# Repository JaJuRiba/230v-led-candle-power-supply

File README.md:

# 230 V Mains-Powered LED Candle Supply — V1

**Concept only. No 230 V schematic, installation approval, or manufacturing release.**

The eventual design takes 230 V AC mains input and provides a shared, securely configurable, isolated DC voltage for one to five LED candles, with individual protection for each output. A separate Shelly relay is intended to handle scheduling in the eventual installation. The final power-supply rating is open. The first prototype uses only low-voltage DC from an external, isolated, current-limited supply. The reference settings are 3.0 V and 4.5 V; the 1.5–6 V range is optional.

```mermaid
flowchart LR
    A[External isolated DC supply] --> B[Shared voltage regulation and monitoring]
    B --> C[Up to five individually protected outputs]
    C --> D[Reference loads, then LED candles with batteries removed]
```

This diagram describes the V1 goal. The A0 schematic below covers only the DC distributor.

## P1 — enclosed low-voltage controller, first-article candidate

P1 uses an **external isolated regulated 6 V supply**. The printed standalone enclosure is not a flush-mount mains enclosure. The [P1 electronics](hardware/p1/README.md) supersede the E1 bench board as the first-article target. No production qualification, regulatory approval or order is claimed.

- [JLCPCB candidate files and order checks](manufacturing/p1-candidate/README.md) · [sourcing evidence](manufacturing/p1-sourcing/README.md)
- [Enclosure: assembly, H2D print files and clearances](mechanical/p1/README.md) · [separate cable harness](docs/p1-harness.md)
- [Design assumptions](docs/p1-design-contract.md) · [physical acceptance tests](manufacturing/p1-tools/acceptance.md)

## E1 — earlier low-voltage bench prototype

[Open the editable E1 project, BOM and bench test procedure](hardware/e1/README.md). Unlike A0, E1 takes **6.10 V nominal isolated bench DC**, regulates it to a shared 3.0 or 4.5 V, and limits current independently on five outputs. No mains input or independent overvoltage cutoff. [Editable two-layer bench PCB and DRC report](hardware/e1/board/README.md). Unbuilt; not a flush-box layout or manufacturing release.

## Earlier KiCad schematic — revision A0

The [editable DC distributor schematic](230v-led-candle-power-supply.kicad_sch) targets KiCad 10.0.8. J1 receives 3.0 V or 4.5 V directly from an isolated, current-limited bench supply. F1–F5 show where branch protection is intended; no fuses have been selected or approved. A0 does not implement voltage regulation, overvoltage protection, or reverse-polarity protection. It has not been built or tested with candles.

The [A0 ERC report](docs/erc-a0.json) shows zero violations in KiCad 10.0.8. The KiCad netlist also contains all seven expected nets. These checks do not approve the design for construction or installation.

## Low-voltage test plan

**E1 design assumption:** budget 20 mA per candle in normal operation and design the distributor for 50 mA continuous per output at either voltage (250 mA total; up to 1.125 W delivered at 4.5 V). This is available current, not current to force through a candle, a measured peak, or a fuse rating. The final supply must also account for conversion losses, temperature and transient response.

Two commercial examples inform the nominal assumption. The [Goobay 64786 manual](https://www.pollin.de/media/fa/6f/01/1742196926/D521850-B.pdf) specifies one LED per candle and 0.06 W/LED at a 3.0 V operating voltage. The [Goobay 74368 manual](https://www.wentronic.com/media/perfion/perfion-product/74368_Bedienungsanleitung%23Manual.pdf) specifies 0.06 W/LED and 4.5 V operation. Dividing those figures by the respective supply voltage gives 20 mA and 13.3 mA as power equivalents, **not** measured battery-terminal currents. Neither figure establishes startup peaks or covers moving-flame and multi-LED models. Use reference loads until each candle model is characterized; coin-cell candles may rely on cell impedance and are not qualified for direct connection.

| Setpoint | Load per output | Current per output | Total current for five outputs | Power per load |
|---|---:|---:|---:|---:|
| 3.0 V | 150 Ω | 20.0 mA | 100.0 mA | 0.060 W |
| 3.0 V | 60 Ω | 50.0 mA | 250.0 mA | 0.150 W |
| 4.5 V | 225 Ω | 20.0 mA | 100.0 mA | 0.090 W |
| 4.5 V | 91 Ω | 49.45 mA | 247.25 mA | 0.223 W |

The figures follow from I = V/R and P = V²/R. Use 1% resistors rated for at least 0.5 W, with adequate ventilation and appropriate derating. These are reference loads, not measured candle characteristics. The test plan does not cover 6 V.

1. At each setpoint, test with no load, one output loaded, and five outputs loaded. Test power-up and load steps. Record current, temperature, and voltage at the supply or regulator and at the farthest load. Use an oscilloscope to capture brief spikes.
2. After branch protection has been implemented, use only reference loads and a current-limited source to test a short on one output. Record the fault current and the behavior of the other outputs. The target is to limit or disconnect the faulty output without driving the others outside their acceptable range. Verify this with the common supply current limit in effect.
3. Evaluate reverse polarity, incorrect voltage selection, and regulator failure separately. Overvoltage protection must match the selected output: a fixed 6 V threshold cannot protect a 3 V candle. Record overload behavior and temperature. No hardware tests have been performed yet.
4. For each selected candle, check polarity, steady-state and peak currents, timer behavior, and restart after loss of power. A regulated supply can deliver more current than a coin cell; nominal battery voltage alone is not enough. Remove batteries before applying external power. Establish acceptable voltage and current limits before finalizing the design.

## Flush-mount box fit study

[Print the two M0 fit gauges and follow the loose-box test](mechanical/README.md). Digitally checked. In one physical trial, the operator reported that the printed bodies went in loosely in the tested orientation. Remaining depth and fit with the cover were not measured. These blocks represent only the relay and module bodies, not the complete assembly.

The reference box is the **KAISER UP¹ 1555-05** (EAN 4013456594937). The [KAISER data sheet](https://www.kaisergroup.com/assets/media/21/21577/Datasheet_1555-05_%28EAN_4013456594937%29_en_KAISER.pdf) lists a 66 mm product depth, a 60 mm diameter device opening, an 82 mm diameter wall cutout, and four groups of three screw bosses. The 82 mm dimension is not an internal diameter. [Elektrikshop](https://www.elektrikshop.de/kaiser-unterputzdosen-up1-1555-05-tief.html) lists 65 mm of internal depth; that is not the usable space after adding a cover, terminals, and wiring.

The reported clear width and usable depth are approximately **54 mm and 64 mm**, respectively. The [to-scale preliminary fit study](fit-study-1555-05.svg) assumes an ideal cylinder; a 54 mm clear diameter across its full depth has not been established. The [KAISER CAD portal entry](https://kaiser.partcommunity.com/?languageIso=en&catalog=kaiser&part=1555-05) is available, but the model download was blocked in this environment.

The [Shelly 1 Mini Gen3](https://www.shelly.com/products/shelly-1-mini-gen3) measures 29 × 34 × 16 mm nominally. The [PCB-mount Mean Well IRM-03](https://www.meanwell.com/Upload/PDF/IRM-03/IRM-03-SPEC.PDF) measures 37 × 24 × 15 mm. Their footprint diagonals are 44.7 mm and 44.1 mm, respectively, so each bare bounding box fits in the idealized cross-section on its own. Their thicknesses add up to 31 mm. The remaining 33 mm is a nominal depth budget, not confirmed clearance: it excludes the PCB, pins, enclosure, terminals, cable routing, and required spacing. This is not a proposed mounting arrangement or proof of fit.

A 3D study must account for the actual box profile, cover, screw bosses, relay, power supply, PCB, enclosure, terminals, and cable bends. Check the insertion path, terminal access, and collisions. Geometric fit does not establish electrical separation, protection against contact, or adequate cooling. A remotely mounted supply remains an option. A qualified electrician must assess the fixed installation, including the applicable overvoltage category, protection, and enclosure, before any mains PCB layout or installation.

## Components and manufacturing

Preliminary candidates: [Mean Well IRM-03-5 / IRM-03-9](https://www.meanwell.com/Upload/PDF/IRM-03/IRM-03-SPEC.PDF), [Diodes AP63201WU-7](https://www.diodes.com/part/view/AP63201), and [Shelly 1 Mini Gen3](https://www.shelly.com/products/shelly-1-mini-gen3). The IRM-03's overvoltage category II rating does not by itself establish suitability for this installation. A buck converter cannot produce 6 V from a 5 V input. Producing 4.5 V from 5 V requires verifying regulation headroom under supply tolerances and load. No power module has been selected.

For JLCPCB assembly, verify availability, LCSC part numbers, footprints, polarity, and the planned SMT or through-hole process before ordering. Generate Gerbers, the BOM, and component placement data only from the reviewed design. Open inputs: usable box geometry, the actual candle model, maximum cable length, and connector type.

See the [development plan](docs/development-plan.md) for the remaining work.

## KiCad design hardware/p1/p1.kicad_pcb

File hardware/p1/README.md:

# P1 — isolated DC five-output distributor

**CAD-checked prototype, not released for ordering, installation or candle use.** Open [p1.kicad_pro](p1.kicad_pro): [editable schematic](p1.kicad_sch), [routed PCB](p1.kicad_pcb), [schematic SVG](preview/p1.svg), [top copper](preview/front.svg), [bottom copper, viewed through board](preview/back.svg), [assembled STEP](mechanical/p1.step). [BOM with exact MPNs](bom.csv), [ERC](erc.rpt), [saved-board DRC including parity](drc.rpt), [independent pin/assembly audit](audit.py). No 230 V circuitry. Keep mains switching, source and wiring outside the printed case.

## Mechanical and harness interface

|Target|P1 design achieved / qualification gap|
|---|---|
|38 × 34 × 1.6 mm, slide-in|Rectangular straight Edge.Cuts from **(100,80) to (138,114) mm** in KiCad. No mounting holes, no bottom components. Reserve first/last 1 mm of X for insulating edge guides. Copper is **not** a mechanical insulation surface. Provide a stop and lid restraint; verify board-thickness tolerance, insertion and extraction with both plugs. No assumed enclosure offset in Z.|
|Four layers|JLC04161H-7628 1.6 mm class, 1 oz outer / 0.5 oz inner nominal. F signal plus GND spreader / In1 continuous GND / In2 VSEL / B GND with short signal crossovers, **not** a pure bottom plane. Standard stack geometry copied, not impedance-designed. Confirm chosen stack option at quotation.|
|One cable exit|One keyed 2-way DC input and a different-width keyed 10-way five-pair output, both horizontal JST SH, toward **+Y**. Bundle and strain-relieve both leads at one exit, do not use SMT hold-downs for strain relief. Mate/service only with cover open and power off.|
|50 mA × 5|Shared selectable voltage rail and five independent fault-limited outputs; not five LED current sources. 250 mA design load, 0.75/1.125 W delivered. Not tested.|

Coordinates below are **mm from top-left outline, looking down on components, +X right, +Y toward plugs**. Add (100,80) for absolute PCB coordinates. STEP export subtracts that XY origin and STEP +Y is opposite KiCad +Y. Register case geometry to the board solid rather than assuming its Z datum. All footprint placement rotations 0°. J1 center (6,30.7), J2 center (25,30.7). Signal lands at Y=28.7. Each anchor pair (MP) is grounded, not a harness terminal.

|Function|Switch pin|J pin + / return|Pad X + / return|
|---|---|---|---|
|6 V input|Q1 drain|J1.1 / J1.2|5.5 / 6.5|
|OUT1|U2.6|J2.1 / J2.2|20.5 / 21.5|
|OUT2|U3.6|J2.3 / J2.4|22.5 / 23.5|
|OUT3|U4.6|J2.5 / J2.6|24.5 / 25.5|
|OUT4|U5.6|J2.7 / J2.8|26.5 / 27.5|
|OUT5|U6.6|J2.9 / J2.10|28.5 / 29.5|

BOM J1/J2 **SM02B-SRSS-TB(LF)(SN)** / **SM10B-SRSS-TB(LF)(SN)**. Mate **SHR-02V-S-B** / **SHR-10V-S-B**, contacts **SSH-003T-P0.2-H**. [JST SH series drawing](https://www.jst-mfg.com/product/pdf/eng/eSH.pdf): side-entry header mounting height 2.95 mm; nominal bodies 4/12 mm wide; pitch 1 mm, 50 V, 1 A with AWG28. Use AWG28 stranded copper in the contact's 0.4–0.8 mm insulation range. Do **not** crimp 0.14 mm² cable directly: splice short keyed pigtails to ≥0.14 mm² trunk/branch cable outside the guide path. At 1 m each way, 0.14 mm² copper alone drops ~12.5 mV at 50 mA; add crimps, pigtails, splices, temperature and switch loss. Continuity-test cavity numbers from mating drawing: wire-side views can be mirrored. P1 does not supply crimp assemblies. Allocate a provisional 12 mm straight service space beyond +Y edge then route bends; verify actual extraction stroke, wire bend and gland with hardware. Plug body/cable absent from STEP. Tallest expected package is U1 DDPAK (reserve 5 mm above board, plus lid and assembly tolerance). Measure first article before fixing enclosure tolerances.

## Power and fault budgets

Specify a **separately qualified regulated isolated 6 V SELV adapter**, 1 A class. J1 operating envelope **5.70–6.30 V at the pins including ripple and leads**, no-load to load; do not substitute an unregulated wall wart. Example sourcing family: [GlobTek GTM41134-06VV-Q](https://www.globtek.com/ds/medical-ict-ite-household-use-power-supply/wall-plug-in/Xhu9OyH7tBZ/Ud5MWJvTD-Q/gtm41134-06vv-q.html), specify 6.0 V/1 A, regional plug and certified configuration. Family approvals are not approval of a particular adapter/harness; require certificate, exact order code and measured tolerance/start/stop behavior. A ±5% DC tolerance **plus** separate ripple/overshoot is not automatically within contract. TPS2553 switches operate only to 6.5 V even in a regulator pass fault. No surge suppressor or input overvoltage disconnect. Initially use isolated, current-limited bench DC (50 mA unloaded; 0.45 A when loading).

* **Q1 AO3401A** G1=return, S2=protected VIN, D3=raw positive. Body diode conducts D→S at correct polarity, channel then enhances; reversed J1 leaves it off. Not reverse-current isolation with externally driven outputs. At 0.4 A, 60 mΩ at −4.5 V gives 24 mV at datasheet test temperature; budget **60 mV total** to U1 including copper, contact variation and hot RDS(on), verify in situ.
* **U1 LT1963AEQ#TRPBF**, adjustable E-grade DDPAK, **1 SHDN tied high, 2 IN, 3 GND and tab, 4 OUT, 5 ADJ**. Q package, not E1's live-tab 1117. C1 local 1 µF, C2 positive pin 1 at OUT, 22 µF 16 V tantalum (19.8 µF initial min); local C3–C7 are extra upstream ceramics. Confirm actual impedance, low-temperature ESR, biased capacitance and load-step stability. At minimum source and guarded high maximum, 5.70−0.060−4.659 = **0.981 V** vs 0.35 V maximum dropout at 0.5 A; even the 1.5 A maximum 0.55 V leaves margin. Nominal headroom isn't the criterion.
* Top feedback R1=1.47 kΩ; lower R2=1.00 kΩ permanently connected. JP1 closes R3=1.18 kΩ to GND in parallel with R2. Divider draws ≥1.17 mA, above 1 mA reference test floor even with open outputs. ADJ bias flows into pin. R9 samples pre-switch rail on VSEL copper independently of ADJ; R10 permanent ground return. R11=**17.4 kΩ**, changed from study's 18.2 kΩ: original high minimum release around 4.653 V can be below this regulator's normal upper corner. JP2 closes independent OVP lower leg. No fault output is fed back into U1 regulation.
* **U7 TPS3700DDCR**: 1 OUTA NC, 2 GND, 3 INA+ GND, 4 INB− midpoint, 5 VDD protected input with C8 100 nF, 6 OUTB open-drain BR_EN. R12 10 kΩ pulls BR_EN to VSEL. **U2–U6 TPS2553DBVR**: 1 IN=VSEL, 2 GND, 3 EN=BR_EN (not tied to IN), 4 FAULT NC, 5 ILIM via own 210 kΩ, 6 distinct OUT. DBV max 135 mΩ ⇒ 6.75 mV at 50 mA before wiring. Both TI parts have pin 1 upper-left counterclockwise numbering (DDC thin vs DBV regular; generic six-lead model for U7). Monitor pulls low against <0.65 mA in a bounded pass fault; compare VOL 0.25 V vs EN low 0.66 V. Released EN ≳2.86 V vs high threshold 1.1 V. Measure each EN.

|JP1 / JP2, both changed unpowered|Nominal VSEL|DC VSEL corners|Disable rising|Release falling|
|---|---:|---:|---:|---:|
|Open / open (as produced)|2.993 V|2.892–3.100 V|3.212–3.308 V|3.139–3.276 V|
|Bridged / bridged|4.500 V|4.348–4.659 V|4.833–4.975 V|4.723–4.926 V|

[audit.py](audit.py) enumerates ±0.20% precision resistors (0.1% initial, 25 ppm/K over ±40 K), 0–1 Ω closed link, ADJ 1.174–1.246 V and 0–10 µA bias; TPS3700 rise 396–404 mV, fall 387–400 mV, design allowance ±50 nA sense leakage. DC windows exclude copper and ripple. Minimum normal-to-release margin is only ~39 mV low; qualify in case. Wrong high setting with both bridged is **not detected**. JP1 closed alone disables branches; JP2 closed alone leaves low output with the wrong high threshold. No latching, no discharge, no protection from a shorted switch or failed-low sense. Monitor can float EN high during startup/UVLO. A fast step can reach nearly fault VIN before shutdown. Threshold is **not** a peak-voltage guarantee. See [prior OVP study and bounded stimulus procedure](../../docs/ovp-study/README.md).

**Single short and heat:** 210 kΩ ±1.5% effective gives ~109–153 mA calculated DC limit; budget 154 mA. Four healthy branches + one short = 354 mA; add ≤4 mA divider, switch and detector overhead plus 25 mA regulator ground-current allowance (0.5 A test point) ⇒ **≤383 mA estimated**. Healthy-case budget ≤279 mA input. Limit calculations are not peak-current or fault-selectivity guarantees. Worst low-mode U1 loss ≈1.03 W full load, ≈1.38 W with one short; high-mode full load ≈0.66 W, including 0.158 W ground-current allowance. To keep TJ below 125 °C at 35 °C air requires effective θJA below ~88 °C/W full low, ~65 °C/W in one low-mode short. DDPAK has solid tab-to-front-ground spreader, adjacent stitching, full inner return and back ground copper; do **not** apply datasheet benchmark θJA as measured compact-enclosure performance. High-mode switch short can dissipate ~0.72 W locally; TI DBV benchmark 182.6 °C/W implies ~131 °C rise, so expect thermal cycling. Stop prolonged faults. Check U1, all switches and case to thermal equilibrium with measured ambient; design does not guarantee continuous short survival.

## Acceptance gates still open

Start with dummy loads only; no cells installed. Both modes: no load, 1 and 5 × 20/50 mA, both input extremes, startup, brownout, cable extremes and repeated branch faults. Use ≥0.5 W 60 Ω / 90 Ω resistors for nominal 50 mA low/high or programmable loads. Rotate fault across J2 pairs; record rail, all healthy far-end minima, short peak/DC, reset and temperatures. For OVP fault injection use a separate isolated test fixture or physically isolate U1 OUT before externally driving VSEL; **never parallel two supplies or force a live LDO output**. Capture EN and far-end peaks, pulse duration, automatic restart and decay at several downstream capacitances. Test all four link states. No real candle until its own permitted DC/transient envelope, polarity and impedance needs are known. No thermal, electrical or enclosure bench result claimed.

All populated parts top-side SMT; JP1/JP2 are **open copper features, not placed parts**. Candidate JLC catalog leads: [U1 C459702](https://jlcpcb.com/partdetail/AnalogDevices-LT1963AEQTRPBF/C459702), [U2–U6 C55266](https://jlcpcb.com/partdetail/C55266), [U7 C33002](https://jlcpcb.com/partdetail/C33002), [Q1 C15127](https://jlcpcb.com/partdetail/C15127). Verify exact MPN, stock, tape variant, rotations, connector mating direction/anchor solder, polarized C2 and U1 stencil/thermal pad. Do not substitute TPS2553-1 or fixed-output LT1963A. No DFM, quotes, stock reservation or assembly release. External supplier/crimp tooling and strain relief remain system items.

Sources: [ADI LT1963A pin configuration, electrical tables and applications](https://www.analog.com/media/en/technical-documentation/data-sheets/lt1963a.pdf); [AO3401A](https://www.aosmd.com/sites/default/files/res/data_sheets/AO3401A.pdf); [TI TPS3700](https://www.ti.com/lit/ds/symlink/tps3700.pdf); [TI TPS2553](https://www.ti.com/lit/ds/symlink/tps2553.pdf); [JLC stack catalog](https://jlcpcb.com/impedance). For the changed U1 test grade, R3 qualification and five-board allocation instructions see the [P1 sourcing override](../../manufacturing/p1-sourcing/README.md). See [build provenance](PROVENANCE.md).

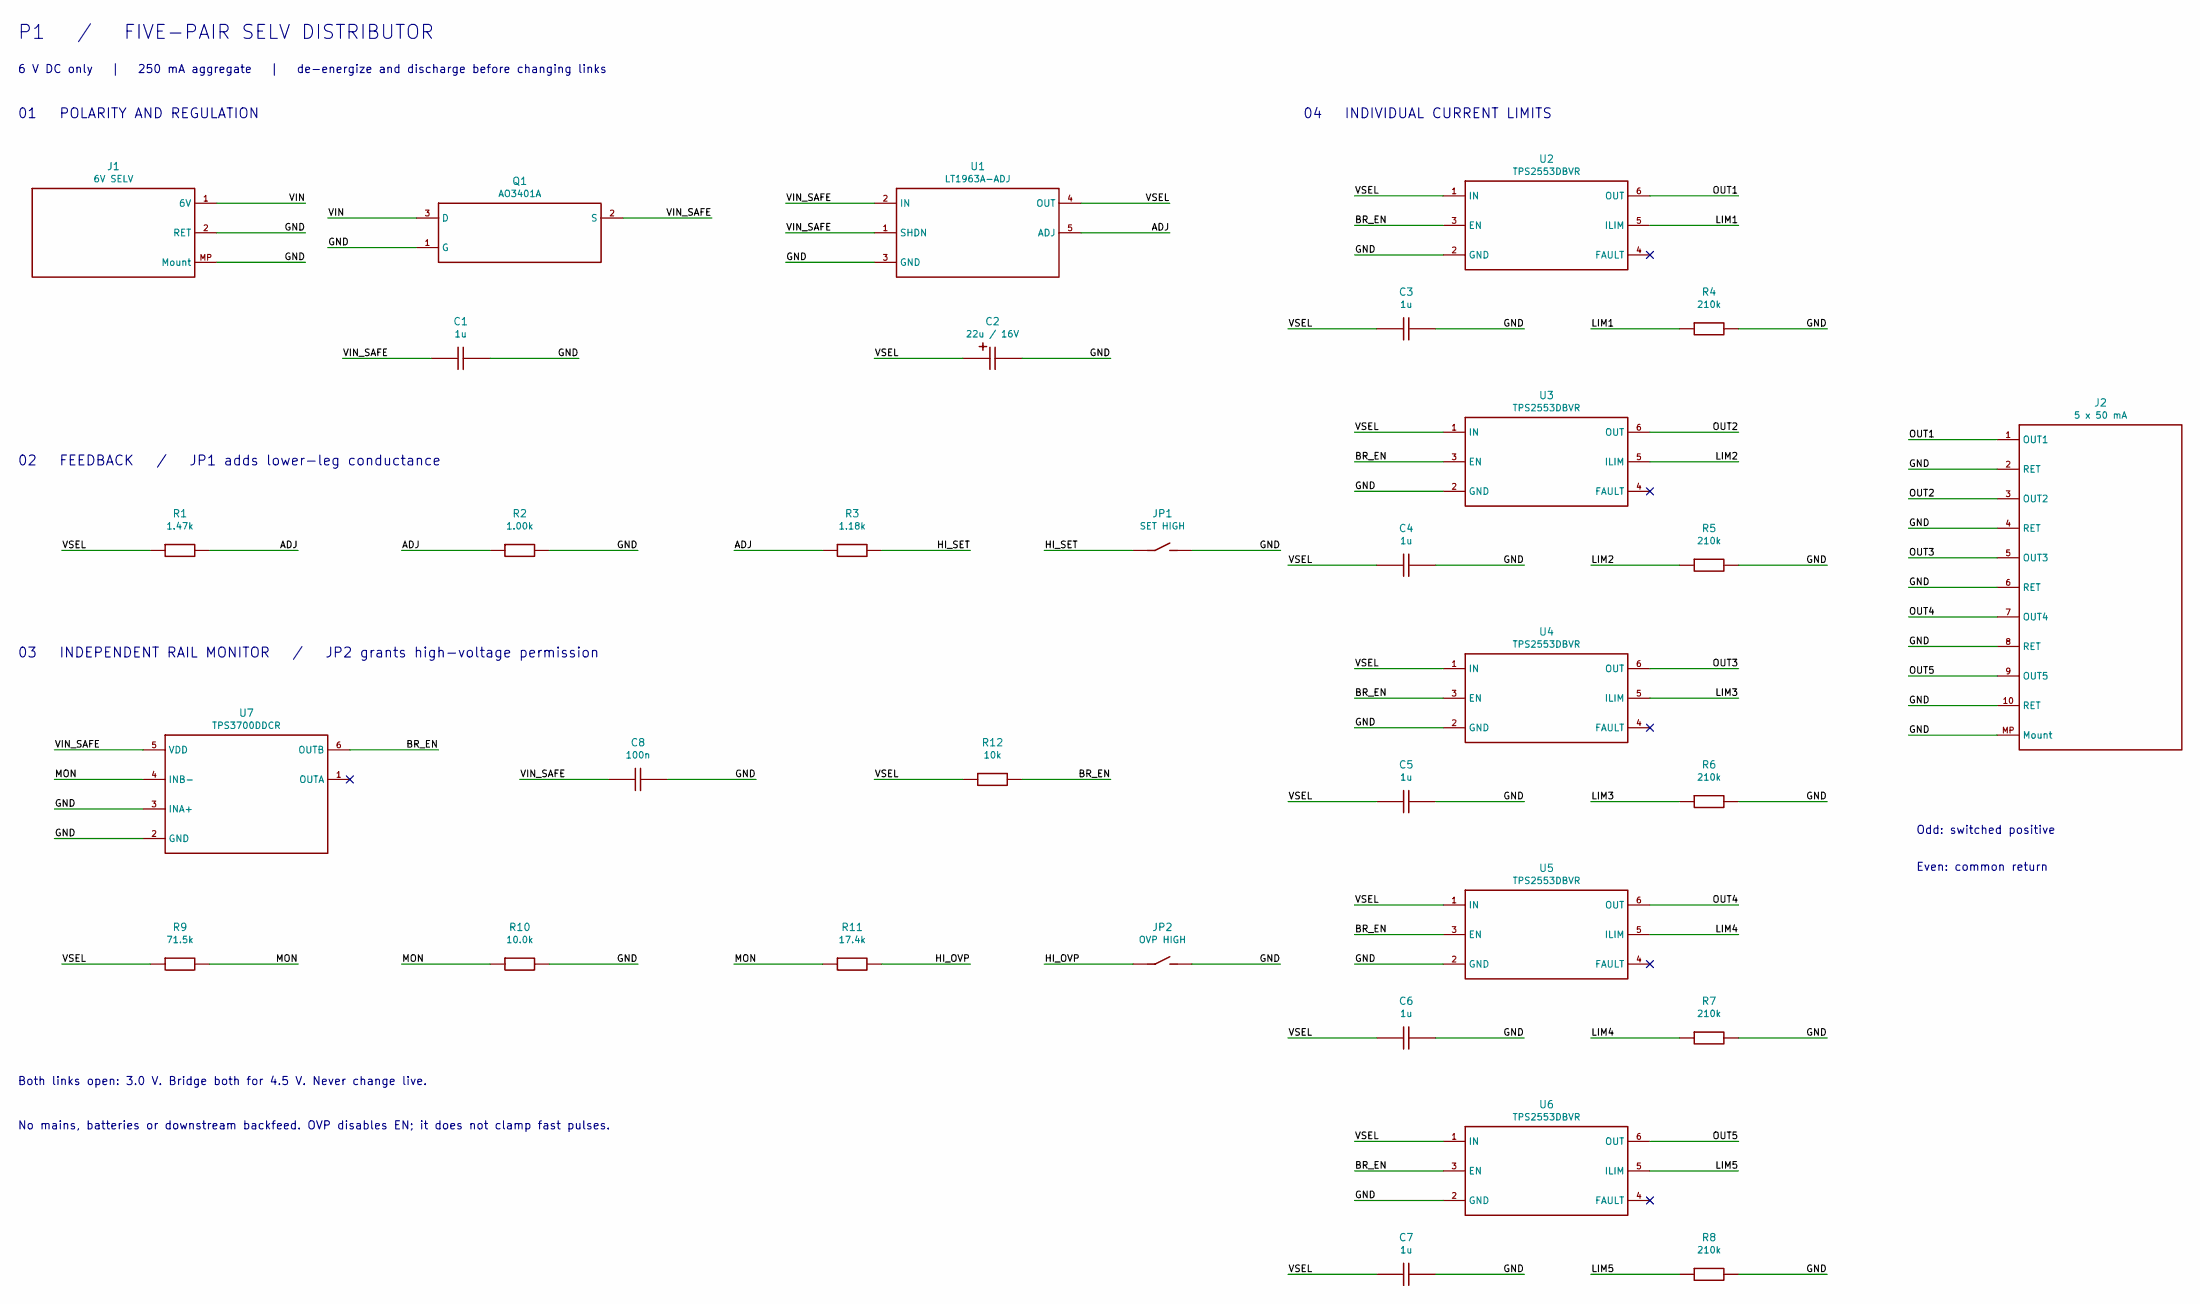
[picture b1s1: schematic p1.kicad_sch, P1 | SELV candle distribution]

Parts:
C1, C3, C4, C5, C6, C7: 1u; C_0805_2012Metric; MPN C0805C105K3RACTU
C2: 22u / 16V; CP_EIA-6032-28_Kemet-C; MPN T491C226K016AT
C8: 100n; C_0805_2012Metric; MPN C0805C104K5RACTU
J1: 6V SELV; JST_SH_SM02B-SRSS-TB_1x02-1MP_P1.00mm_Horizontal; MPN SM02B-SRSS-TB(LF)(SN)
J2: 5 x 50 mA; JST_SH_SM10B-SRSS-TB_1x10-1MP_P1.00mm_Horizontal; MPN SM10B-SRSS-TB(LF)(SN)
JP1: SET HIGH; SolderJumper-2_P1.3mm_Open_Pad1.0x1.5mm; MPN PCB copper - open
JP2: OVP HIGH; SolderJumper-2_P1.3mm_Open_Pad1.0x1.5mm; MPN PCB copper - open
Q1: AO3401A; SOT-23; MPN AO3401A
R1: 1.47k; R_0805_2012Metric; MPN RT0805BRD071K47L
R2: 1.00k; R_0805_2012Metric; MPN RT0805BRD071KL
R3: 1.18k; R_0805_2012Metric; MPN PTFR0805B1K18P9
R4, R5, R6, R7, R8: 210k; R_0805_2012Metric; MPN RC0805FR-07210KL
R9: 71.5k; R_0805_2012Metric; MPN RT0805BRD0771K5L
R10: 10.0k; R_0805_2012Metric; MPN RT0805BRD0710KL
R11: 17.4k; R_0805_2012Metric; MPN RT0805BRD0717K4L
R12: 10k; R_0805_2012Metric; MPN RC0805FR-0710KL
U1: LT1963A-ADJ; TO-263-5_TabPin3; MPN LT1963AEQ#TRPBF
U2, U3, U4, U5, U6: TPS2553DBVR; SOT-23-6; MPN TPS2553DBVR
U7: TPS3700DDCR; SOT-23-6; MPN TPS3700DDCR

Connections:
/ADJ: R1.2, R2.1, R3.1, U1.5 (ADJ)
/BR_EN: R12.2, U2.3 (EN), U3.3 (EN), U4.3 (EN), U5.3 (EN), U6.3 (EN), U7.6 (OUTB)
/GND: C1.2, C2.2, C3.2, C4.2, C5.2, C6.2, C7.2, C8.2, J1.2 (RET), J1.MP (Mount), J2.2 (RET), J2.4 (RET), J2.6 (RET), J2.8 (RET), J2.10 (RET), J2.MP (Mount), JP1.2, JP2.2, Q1.1 (G), R2.2, R4.2, R5.2, R6.2, R7.2, R8.2, R10.2, U1.3 (GND), U2.2 (GND), U3.2 (GND), U4.2 (GND), U5.2 (GND), U6.2 (GND), U7.2 (GND), U7.3 (INA+)
/HI_OVP: JP2.1, R11.2
/HI_SET: JP1.1, R3.2
/LIM1: R4.1, U2.5 (ILIM)
/LIM2: R5.1, U3.5 (ILIM)
/LIM3: R6.1, U4.5 (ILIM)
/LIM4: R7.1, U5.5 (ILIM)
/LIM5: R8.1, U6.5 (ILIM)
/MON: R9.2, R10.1, R11.1, U7.4 (INB-)
/OUT1: J2.1 (OUT1), U2.6 (OUT)
/OUT2: J2.3 (OUT2), U3.6 (OUT)
/OUT3: J2.5 (OUT3), U4.6 (OUT)
/OUT4: J2.7 (OUT4), U5.6 (OUT)
/OUT5: J2.9 (OUT5), U6.6 (OUT)
/VIN: J1.1 (6V), Q1.3 (D)
/VIN_SAFE: C1.1, C8.1, Q1.2 (S), U1.1 (SHDN), U1.2 (IN), U7.5 (VDD)
/VSEL: C2.1, C3.1, C4.1, C5.1, C6.1, C7.1, R1.1, R9.1, R12.1, U1.4 (OUT), U2.1 (IN), U3.1 (IN), U4.1 (IN), U5.1 (IN), U6.1 (IN)

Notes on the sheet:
P1 / FIVE-PAIR SELV DISTRIBUTOR
6 V DC only | 250 mA aggregate | de-energize and discharge before changing links
01 POLARITY AND REGULATION
02 FEEDBACK / JP1 adds lower-leg conductance
03 INDEPENDENT RAIL MONITOR / JP2 grants high-voltage permission
Both links open: 3.0 V. Bridge both for 4.5 V. Never change live.
No mains, batteries or downstream backfeed. OVP disables EN; it does not clamp fast pulses.
04 INDIVIDUAL CURRENT LIMITS
Odd: switched positive
Even: common return

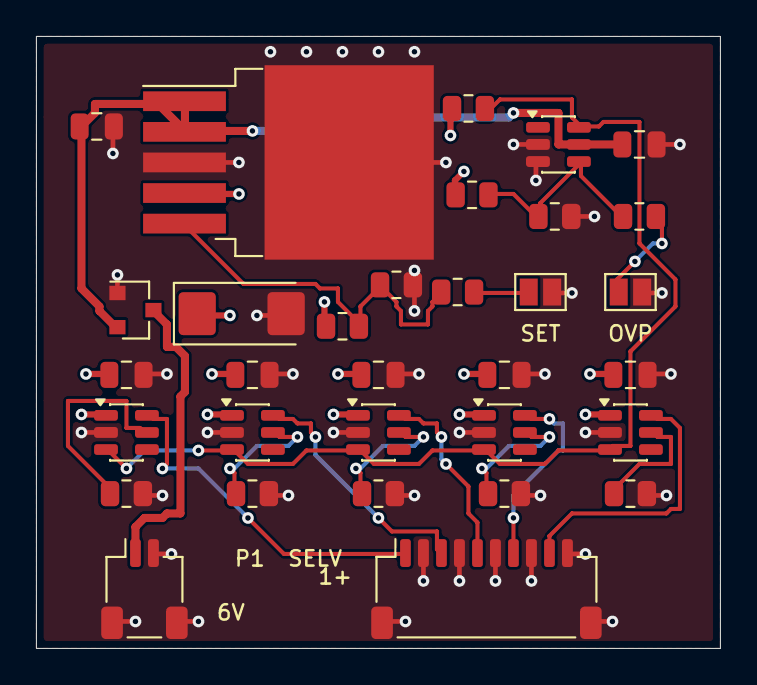
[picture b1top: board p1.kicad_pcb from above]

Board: 4 copper layers, 38.0 x 34.0 mm, 32 parts (0 on the bottom side), 19 nets.

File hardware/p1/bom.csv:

Reference,Value,MPN,Footprint
J1,6V SELV,SM02B-SRSS-TB(LF)(SN),Connector_JST:JST_SH_SM02B-SRSS-TB_1x02-1MP_P1.00mm_Horizontal
Q1,AO3401A,AO3401A,Package_TO_SOT_SMD:SOT-23
U1,LT1963A-ADJ,LT1963AEQ#TRPBF,Package_TO_SOT_SMD:TO-263-5_TabPin3
C1,1u,C0805C105K3RACTU,Capacitor_SMD:C_0805_2012Metric
C2,22u / 16V,T491C226K016AT,Capacitor_Tantalum_SMD:CP_EIA-6032-28_Kemet-C
R1,1.47k,RT0805BRD071K47L,Resistor_SMD:R_0805_2012Metric
R2,1.00k,RT0805BRD071KL,Resistor_SMD:R_0805_2012Metric
R3,1.18k,PTFR0805B1K18P9,Resistor_SMD:R_0805_2012Metric
JP1,SET HIGH,PCB copper - open,Jumper:SolderJumper-2_P1.3mm_Open_Pad1.0x1.5mm
U7,TPS3700DDCR,TPS3700DDCR,Package_TO_SOT_SMD:SOT-23-6
C8,100n,C0805C104K5RACTU,Capacitor_SMD:C_0805_2012Metric
R12,10k,RC0805FR-0710KL,Resistor_SMD:R_0805_2012Metric
R9,71.5k,RT0805BRD0771K5L,Resistor_SMD:R_0805_2012Metric
R10,10.0k,RT0805BRD0710KL,Resistor_SMD:R_0805_2012Metric
R11,17.4k,RT0805BRD0717K4L,Resistor_SMD:R_0805_2012Metric
JP2,OVP HIGH,PCB copper - open,Jumper:SolderJumper-2_P1.3mm_Open_Pad1.0x1.5mm
U2,TPS2553DBVR,TPS2553DBVR,Package_TO_SOT_SMD:SOT-23-6
C3,1u,C0805C105K3RACTU,Capacitor_SMD:C_0805_2012Metric
R4,210k,RC0805FR-07210KL,Resistor_SMD:R_0805_2012Metric
U3,TPS2553DBVR,TPS2553DBVR,Package_TO_SOT_SMD:SOT-23-6
C4,1u,C0805C105K3RACTU,Capacitor_SMD:C_0805_2012Metric
R5,210k,RC0805FR-07210KL,Resistor_SMD:R_0805_2012Metric
U4,TPS2553DBVR,TPS2553DBVR,Package_TO_SOT_SMD:SOT-23-6
C5,1u,C0805C105K3RACTU,Capacitor_SMD:C_0805_2012Metric
R6,210k,RC0805FR-07210KL,Resistor_SMD:R_0805_2012Metric
U5,TPS2553DBVR,TPS2553DBVR,Package_TO_SOT_SMD:SOT-23-6
C6,1u,C0805C105K3RACTU,Capacitor_SMD:C_0805_2012Metric
R7,210k,RC0805FR-07210KL,Resistor_SMD:R_0805_2012Metric
U6,TPS2553DBVR,TPS2553DBVR,Package_TO_SOT_SMD:SOT-23-6
C7,1u,C0805C105K3RACTU,Capacitor_SMD:C_0805_2012Metric
R8,210k,RC0805FR-07210KL,Resistor_SMD:R_0805_2012Metric
J2,5 x 50 mA,SM10B-SRSS-TB(LF)(SN),Connector_JST:JST_SH_SM10B-SRSS-TB_1x10-1MP_P1.00mm_Horizontal
